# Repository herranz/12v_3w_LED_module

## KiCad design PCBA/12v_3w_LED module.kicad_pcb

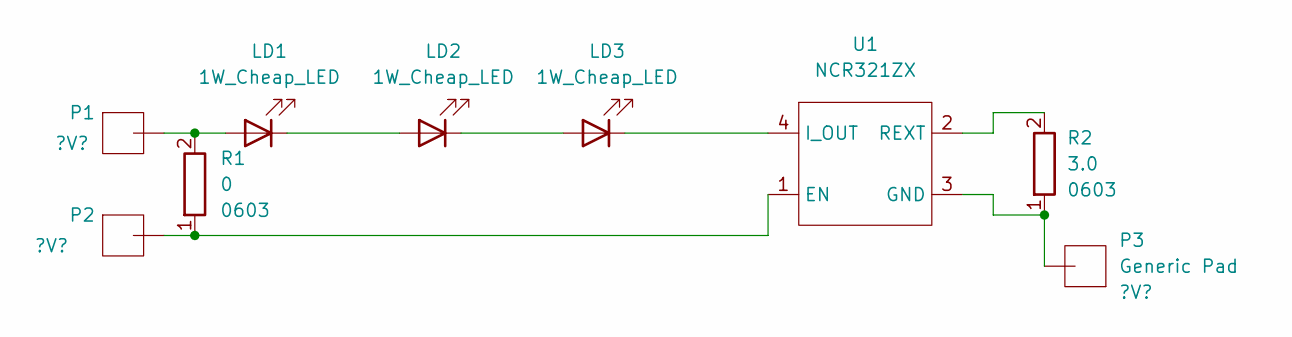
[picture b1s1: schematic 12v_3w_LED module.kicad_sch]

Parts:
LD1, LD2, LD3: 1W_Cheap_LED; 1W_cheap_LED
P1, P2, P3: Generic Pad; Voltage ?V?
R1: 0; R_0603_1608Metric
R2: 3.0; R_0603_1608Metric
U1: NCR321ZX; SOT230P700X180-4N

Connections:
unnamed: LD1.2 (K), LD2.1 (A)
unnamed: LD2.2 (K), LD3.1 (A)
unnamed: LD3.2 (K), U1.4 (I_OUT)
unnamed: LD1.1 (A), P1.1, R1.2
unnamed: P2.1, R1.1, U1.1 (EN)
unnamed: P3.1, R2.1, U1.3 (GND)
unnamed: R2.2, U1.2 (REXT)

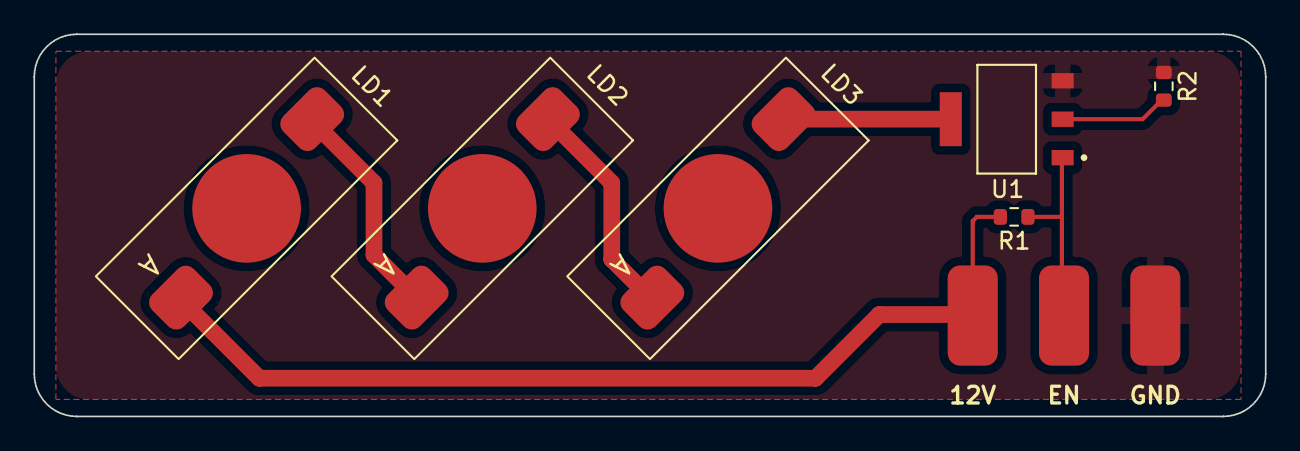
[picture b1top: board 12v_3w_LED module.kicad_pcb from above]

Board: 2 copper layers, 73.7 x 22.9 mm, 9 parts (0 on the bottom side), 7 nets.

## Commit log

2022-01-01 test inicial
2022-01-02 creacion esquematico e inicio de PCB
2022-01-02 completado el diseño de PCB
2022-01-02 modificacion plano de massa
2022-01-03 creadas las reglas de diseñor & DRC correcto
2022-01-04 añadido logo, fillet las esquinas y arreglado la polaridad de los LED
2022-01-06 finalizado el diseño
